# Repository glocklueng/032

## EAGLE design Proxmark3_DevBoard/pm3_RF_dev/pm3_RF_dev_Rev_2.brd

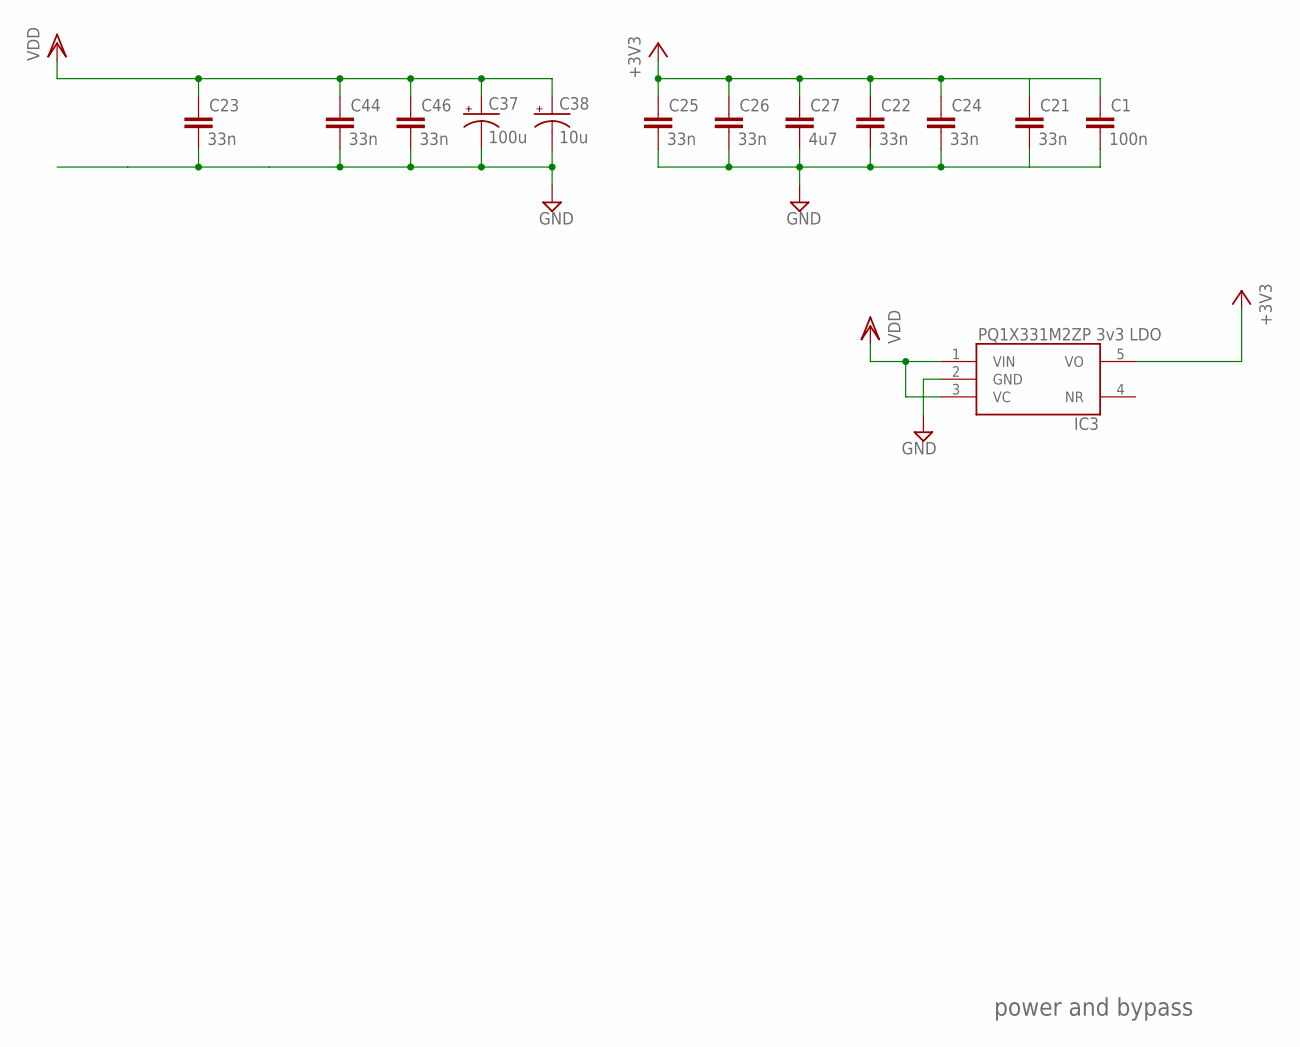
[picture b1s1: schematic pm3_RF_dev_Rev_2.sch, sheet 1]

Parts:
C1: 100n; RLC_0603
C21, C22, C23, C24, C25, C26, C44, C46: 33n; RLC_0603
C27: 4u7; RLC_1210
C37: 100u; CAPCAITOR-ELECTROLYTIC-ALCHIP-MZA-F80
C38: 10u; CAPCAITOR-ELECTROLYTIC-ALCHIP-MZA-F80
IC3: PQ1X331M2ZP-3V3-LDO-SOT-23-5; SOT-23-5

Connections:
+3V3: C1.1, C21.1, C22.1, C24.1, C25.1, C26.1, C27.1, IC3.5 (VO); also elsewhere on the board
GND: C1.2, C21.2, C22.2, C23.2, C24.2, C25.2, C26.2, C27.2, C37.-, C38.-, C44.2, C46.2, IC3.2 (GND); also elsewhere on the board
VDD: C23.1, C37.+, C38.+, C44.1, C46.1, IC3.1 (VIN), IC3.3 (VC); also elsewhere on the board

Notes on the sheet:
power and bypass

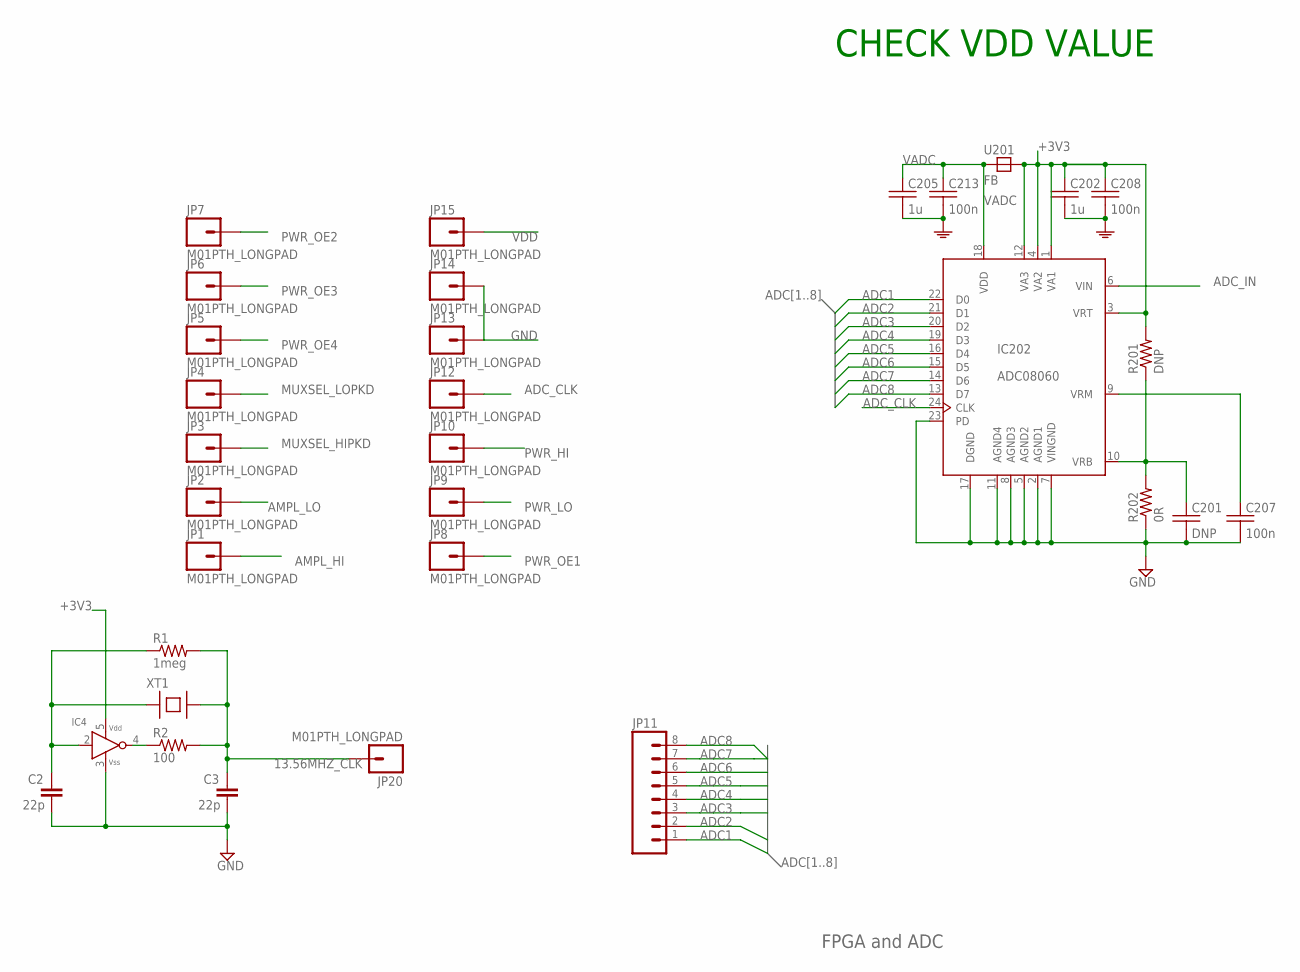
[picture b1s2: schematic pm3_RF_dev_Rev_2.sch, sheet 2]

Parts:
C2, C3: 22p; RLC_0603
C201: DNP; 0603
C202, C205: 1u; 0603
C207, C208, C213: 100n; 0603
IC4: HCU-INVERTER; SMV-5
IC202: ADC08060; TSSOP24
JP1, JP2, JP3, JP4, JP5, JP6, JP7, JP8, JP9, JP10, JP12, JP13, JP14, JP15, JP20: M01PTH_LONGPAD; 1X01_LONGPAD
JP11: M08LONGPADS; 1X08_LONGPADS
R1: 1meg; RLC_0603
R2: 100; RLC_0603
R201: DNP; 0603
R202: 0R; 0603
U201: FB; 0805
XT1: XTAL-SMD-CITIZEN-CS10

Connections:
13.56MHZ_CLK: C3.1, JP20.1, R1.2, R2.2, XT1.B
+3V3: C202.1, C208.1, IC4.5 (VDD), IC202.1 (VA1), IC202.3 (VRT), IC202.4 (VA2), IC202.12 (VA3), R201.2, U201.2 (B); also elsewhere on the board
ADC1: IC202.22 (D0), JP11.1
ADC2: IC202.21 (D1), JP11.2
ADC3: IC202.20 (D2), JP11.3
ADC4: IC202.19 (D3), JP11.4
ADC5: IC202.16 (D4), JP11.5
ADC6: IC202.15 (D5), JP11.6
ADC7: IC202.14 (D6), JP11.7
ADC8: IC202.13 (D7), JP11.8
ADC_CLK: IC202.24 (CLK), JP12.1
ADC_IN: IC202.6 (VIN); also elsewhere on the board
AMPL_HI: JP1.1; also elsewhere on the board
AMPL_LO: JP2.1; also elsewhere on the board
GND: C2.2, C3.2, C201.2, C202.2, C205.2, C207.2, C208.2, C213.2, IC4.3 (VSS), IC202.2 (AGND1), IC202.5 (AGND2), IC202.7 (VINGND), IC202.8 (AGND3), IC202.11 (AGND4), IC202.17 (DGND), IC202.23 (PD), JP13.1, JP14.1, R202.1; also elsewhere on the board
MUXSEL_HIPKD: JP3.1; also elsewhere on the board
MUXSEL_LOPKD: JP4.1; also elsewhere on the board
unnamed: IC4.4 (Y), R2.1
unnamed: C2.1, IC4.2 (A), R1.1, XT1.A
unnamed: C201.1, IC202.10 (VRB), R201.1, R202.2
unnamed: C207.1, IC202.9 (VRM)
PWR_HI: JP10.1; also elsewhere on the board
PWR_LO: JP9.1; also elsewhere on the board
PWR_OE1: JP8.1; also elsewhere on the board
PWR_OE2: JP7.1; also elsewhere on the board
PWR_OE3: JP6.1; also elsewhere on the board
PWR_OE4: JP5.1; also elsewhere on the board
VADC: C205.1, C213.1, IC202.18 (VDD), U201.1 (A)
VDD: JP15.1; also elsewhere on the board

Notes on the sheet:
FPGA and ADC
CHECK VDD VALUE

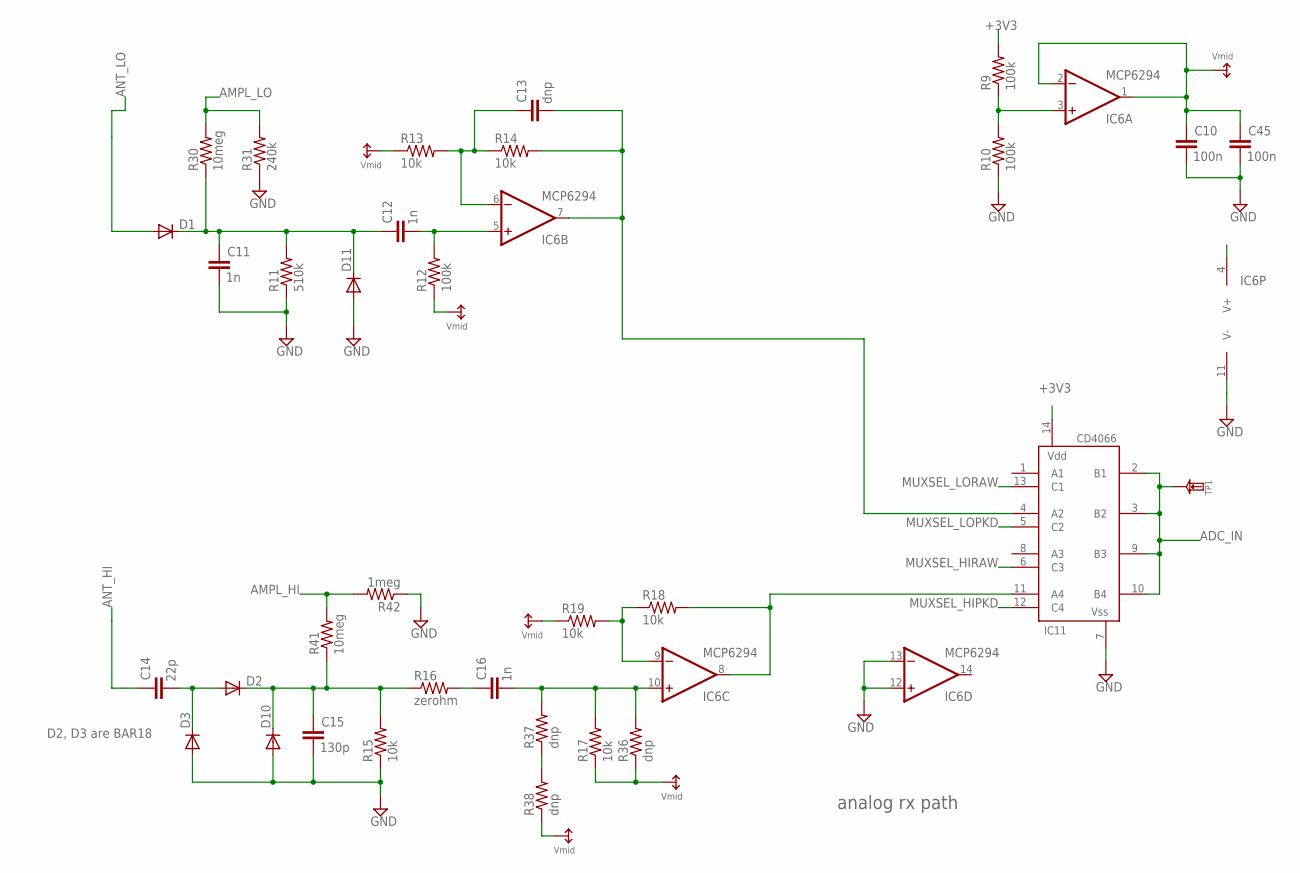
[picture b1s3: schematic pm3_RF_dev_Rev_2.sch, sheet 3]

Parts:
C10, C45: 100n; RLC_0603
C11, C12, C16: 1n; RLC_0603
C13: dnp; RLC_0603
C14: 22p; RLC_0603
C15: 130p; RLC_0603
D1, D2, D3, D10, D11: DIODE-SMD-SOT23; SOT23-3LEAD
IC6: MCP6294; TSSOP-14
IC11: CD4066; TSSOP-14
R9, R10, R12: 100k; RLC_0603
R11: 510k; RLC_0603
R13, R14, R15, R17, R18, R19: 10k; RLC_0603
R16: zerohm; RLC_0603
R30, R41: 10meg; RLC_0603
R31: 240k; RLC_0603
R36, R37, R38: dnp; RLC_0603
R42: 1meg; RLC_0603
TP1: TESTPADKEYSTONE-SMD; KEYSTONE-SMD-TESTPOINT-5015

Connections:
+3V3: IC6.4 (V+), IC11.14 (VDD), R9.2; also elsewhere on the board
ADCDR_HI: IC6.8 (OUT), IC11.11 (A4), R18.2
ADCDR_LO: C13.2, IC6.7 (OUT), IC11.4 (A2), R14.2
ADC_IN: IC11.2 (B1), IC11.3 (B2), IC11.9 (B3), IC11.10 (B4), TP1.1; also elsewhere on the board
AMPL_HI: R41.2, R42.2; also elsewhere on the board
AMPL_LO: R30.2, R31.2; also elsewhere on the board
ANT_HI: C14.1; also elsewhere on the board
ANT_LO: D1.1 (A); also elsewhere on the board
GND: C10.2, C11.2, C15.2, C45.2, D3.1 (A), D10.1 (A), D11.1 (A), IC6.11 (V-), IC6.12 (+IN), IC6.13 (-IN), IC11.7 (VSS), R10.1, R11.1, R15.1, R31.1, R42.1; also elsewhere on the board
MUXSEL_HIPKD: IC11.12 (C4); also elsewhere on the board
MUXSEL_HIRAW: IC11.6 (C3)
MUXSEL_LOPKD: IC11.5 (C2); also elsewhere on the board
MUXSEL_LORAW: IC11.13 (C1)
unnamed: IC6.3 (+IN), R9.1, R10.2
unnamed: IC6.9 (-IN), R18.1, R19.2
unnamed: C12.2, IC6.5 (+IN), R12.2
unnamed: C13.1, IC6.6 (-IN), R13.2, R14.1
unnamed: C16.1, R16.2
unnamed: C11.1, C12.1, D1.3 (C), D11.3 (C), R11.2, R30.1
unnamed: C14.2, D2.1 (A), D3.3 (C)
unnamed: C15.1, D2.3 (C), D10.3 (C), R15.2, R16.1, R41.1
unnamed: C16.2, IC6.10 (+IN), R17.2, R36.2, R37.2
unnamed: R37.1, R38.2
VMID: C10.1, C45.1, IC6.1 (OUT), IC6.2 (-IN), R12.1, R13.1, R17.1, R19.1, R36.1, R38.1

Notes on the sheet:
analog rx path
D2, D3 are BAR18

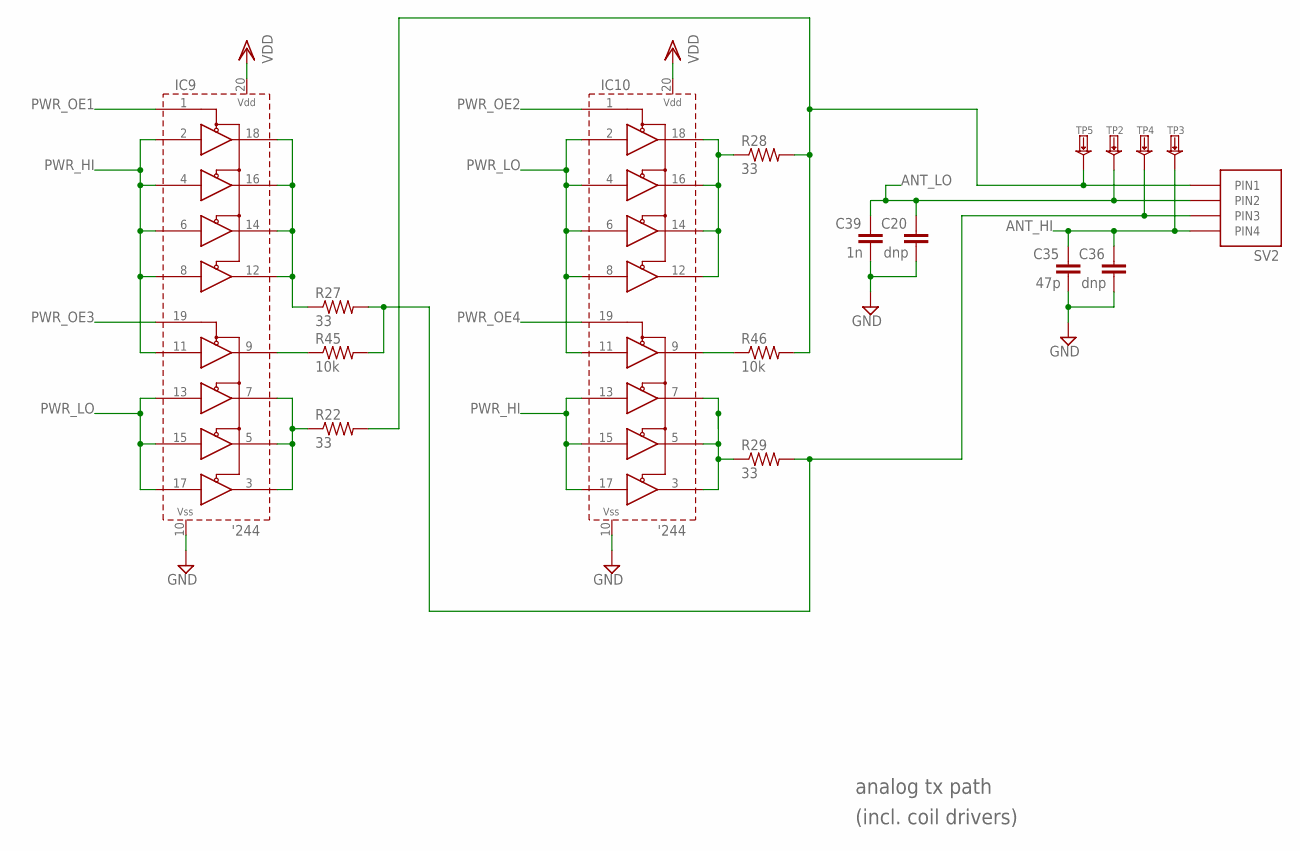
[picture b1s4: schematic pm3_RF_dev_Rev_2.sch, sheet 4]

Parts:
C20, C36: dnp; RLC_0603
C35: 47p; RLC_0603
C39: 1n; RLC_0603
IC9, IC10: 74XX244-OCTAL-TRISTATE-BUFFERS; TSSOP-20
R22, R27, R28, R29: 33; RLC_0603
R45, R46: 10k; RLC_0603
SV2: HIROSE-MQ172-4POS
TP2, TP3, TP4, TP5: TESTPADKEYSTONE-SMD; KEYSTONE-SMD-TESTPOINT-5015

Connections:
ANT_HI: C35.1, C36.1, SV2.4 (PIN4), TP3.1; also elsewhere on the board
ANT_LO: C20.1, C39.1, SV2.2 (PIN2), TP2.1; also elsewhere on the board
GND: C20.2, C35.2, C36.2, C39.2, IC9.10 (VSS), IC10.10 (VSS); also elsewhere on the board
unnamed: R27.2, R29.2, R45.2, SV2.3 (PIN3), TP4.1
unnamed: R22.2, R28.2, R46.2, SV2.1 (PIN1), TP5.1
unnamed: IC9.12 (1Y4), IC9.14 (1Y3), IC9.16 (1Y2), IC9.18 (1Y1), R27.1
unnamed: IC10.12 (1Y4), IC10.14 (1Y3), IC10.16 (1Y2), IC10.18 (1Y1), R28.1
unnamed: IC9.3 (2Y4), IC9.5 (2Y3), IC9.7 (2Y2), R22.1
unnamed: IC10.3 (2Y4), IC10.5 (2Y3), IC10.7 (2Y2), R29.1
unnamed: IC9.9 (2Y1), R45.1
unnamed: IC10.9 (2Y1), R46.1
PWR_HI: IC9.2 (1A1), IC9.4 (1A2), IC9.6 (1A3), IC9.8 (1A4), IC9.11 (2A1), IC10.13 (2A2), IC10.15 (2A3), IC10.17 (2A4); also elsewhere on the board
PWR_LO: IC9.13 (2A2), IC9.15 (2A3), IC9.17 (2A4), IC10.2 (1A1), IC10.4 (1A2), IC10.6 (1A3), IC10.8 (1A4), IC10.11 (2A1); also elsewhere on the board
PWR_OE1: IC9.1 (1NOE); also elsewhere on the board
PWR_OE2: IC10.1 (1NOE); also elsewhere on the board
PWR_OE3: IC9.19 (2NOE); also elsewhere on the board
PWR_OE4: IC10.19 (2NOE); also elsewhere on the board
VDD: IC9.20 (VDD), IC10.20 (VDD); also elsewhere on the board

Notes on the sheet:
analog tx path
(incl. coil drivers)

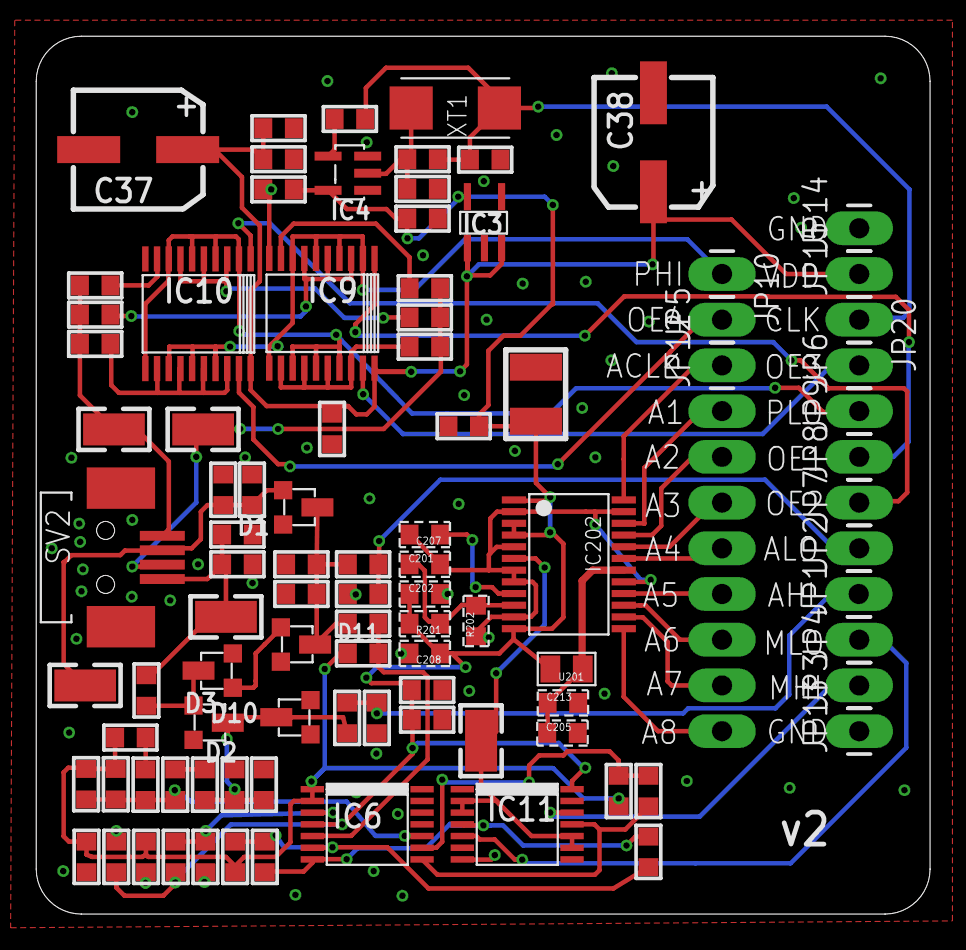
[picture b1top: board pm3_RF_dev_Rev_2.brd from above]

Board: 2 copper layers, 49.7 x 48.8 mm, 96 parts (1 on the bottom side), 52 nets.
